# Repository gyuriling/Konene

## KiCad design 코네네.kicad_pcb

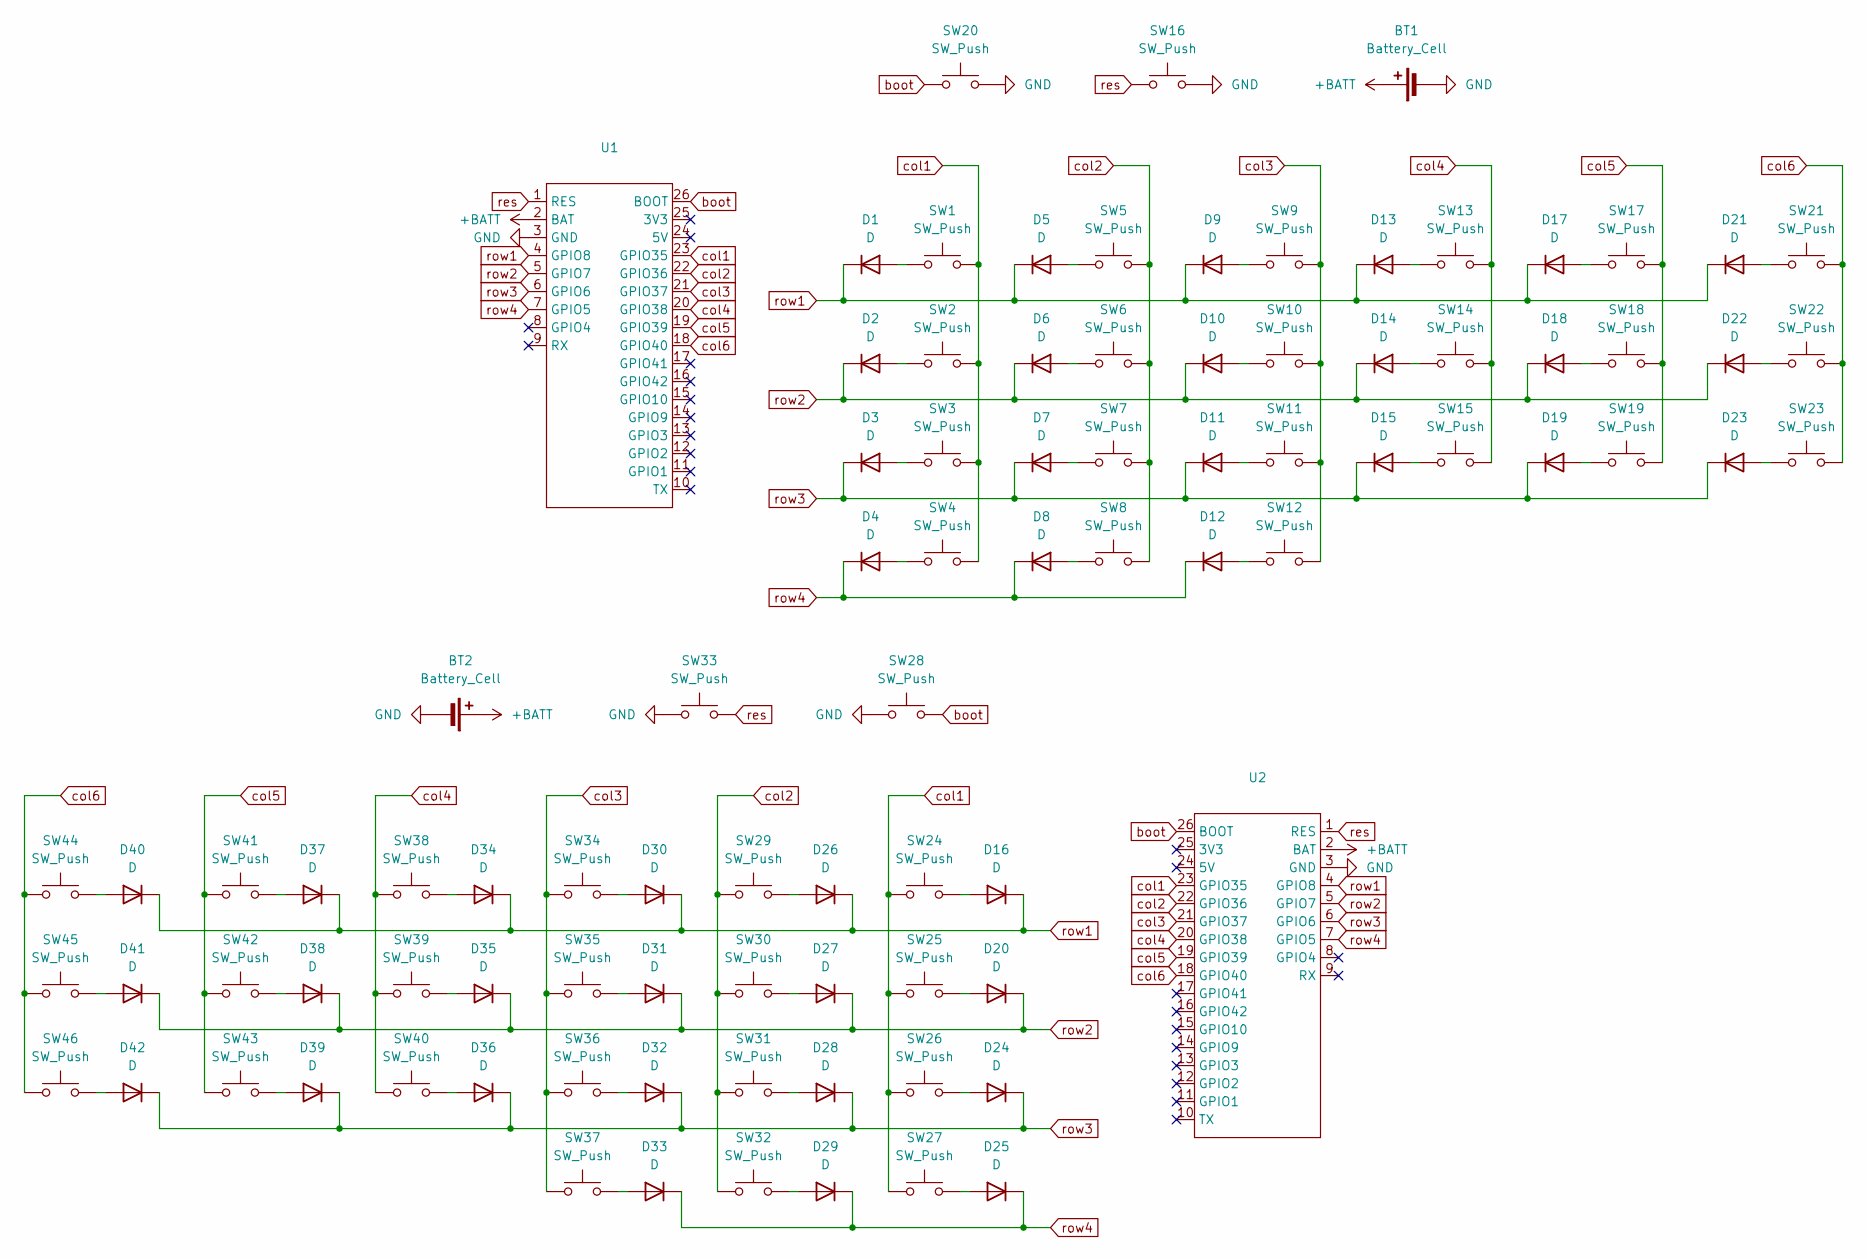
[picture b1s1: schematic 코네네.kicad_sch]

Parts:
BT1, BT2: Battery_Cell; AMASS_XT30U-M_1x02_P5.0mm_Vertical
D1, D2, D3, D4, D5, D6, D7, D8, D9, D10, D11, D12, D13, D14, D15, D16, D17, D18, D19, D20, D21, D22, D23, D24, D25, D26, D27, D28, D29, D30, D31, D32, D33, D34, D35, D36, D37, D38, D39, D40, D41, D42: D; D_SOD-123
SW1, SW2, SW3, SW4, SW5, SW6, SW7, SW8, SW9, SW10, SW11, SW12, SW13, SW14, SW15, SW17, SW18, SW19, SW21, SW22, SW23, SW24, SW25, SW26, SW27, SW29, SW30, SW31, SW32, SW34, SW35, SW36, SW37, SW38, SW39, SW40, SW41, SW42, SW43, SW44, SW45, SW46: SW_Push; Kailh_socket_PG1350
SW16, SW20, SW28, SW33: SW_Push; SW_PUSH_1P1T_6x3.5mm_H4.3_APEM_MJTP1243
U1, U2: esp32_displaykit_s3

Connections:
+BATT: BT1.1 (+), BT2.1 (+), U1.2 (BAT), U2.2 (BAT)
GND: BT1.2 (-), BT2.2 (-), SW16.2, SW20.2, SW28.2, SW33.2, U1.3 (GND), U2.3 (GND)
unnamed: D1.2 (A), SW1.1
unnamed: D2.2 (A), SW2.1
unnamed: D3.2 (A), SW3.1
unnamed: D4.2 (A), SW4.1
unnamed: D5.2 (A), SW5.1
unnamed: D6.2 (A), SW6.1
unnamed: D7.2 (A), SW7.1
unnamed: D8.2 (A), SW8.1
unnamed: D9.2 (A), SW9.1
unnamed: D10.2 (A), SW10.1
unnamed: D11.2 (A), SW11.1
unnamed: D12.2 (A), SW12.1
unnamed: D13.2 (A), SW13.1
unnamed: D14.2 (A), SW14.1
unnamed: D15.2 (A), SW15.1
unnamed: D16.2 (A), SW24.1
unnamed: D17.2 (A), SW17.1
unnamed: D18.2 (A), SW18.1
unnamed: D19.2 (A), SW19.1
unnamed: D20.2 (A), SW25.1
unnamed: D21.2 (A), SW21.1
unnamed: D22.2 (A), SW22.1
unnamed: D23.2 (A), SW23.1
unnamed: D24.2 (A), SW26.1
unnamed: D25.2 (A), SW27.1
unnamed: D26.2 (A), SW29.1
unnamed: D27.2 (A), SW30.1
unnamed: D28.2 (A), SW31.1
unnamed: D29.2 (A), SW32.1
unnamed: D30.2 (A), SW34.1
unnamed: D31.2 (A), SW35.1
unnamed: D32.2 (A), SW36.1
unnamed: D33.2 (A), SW37.1
unnamed: D34.2 (A), SW38.1
unnamed: D35.2 (A), SW39.1
unnamed: D36.2 (A), SW40.1
unnamed: D37.2 (A), SW41.1
unnamed: D38.2 (A), SW42.1
unnamed: D39.2 (A), SW43.1
unnamed: D40.2 (A), SW44.1
unnamed: D41.2 (A), SW45.1
unnamed: D42.2 (A), SW46.1
boot: SW20.1, SW28.1, U1.26 (BOOT), U2.26 (BOOT)
col1: SW1.2, SW2.2, SW3.2, SW4.2, SW24.2, SW25.2, SW26.2, SW27.2, U1.23 (GPIO35), U2.23 (GPIO35)
col2: SW5.2, SW6.2, SW7.2, SW8.2, SW29.2, SW30.2, SW31.2, SW32.2, U1.22 (GPIO36), U2.22 (GPIO36)
col3: SW9.2, SW10.2, SW11.2, SW12.2, SW34.2, SW35.2, SW36.2, SW37.2, U1.21 (GPIO37), U2.21 (GPIO37)
col4: SW13.2, SW14.2, SW15.2, SW38.2, SW39.2, SW40.2, U1.20 (GPIO38), U2.20 (GPIO38)
col5: SW17.2, SW18.2, SW19.2, SW41.2, SW42.2, SW43.2, U1.19 (GPIO39), U2.19 (GPIO39)
col6: SW21.2, SW22.2, SW23.2, SW44.2, SW45.2, SW46.2, U1.18 (GPIO40), U2.18 (GPIO40)
res: SW16.1, SW33.1, U1.1 (RES), U2.1 (RES)
row1: D1.1 (K), D5.1 (K), D9.1 (K), D13.1 (K), D16.1 (K), D17.1 (K), D21.1 (K), D26.1 (K), D30.1 (K), D34.1 (K), D37.1 (K), D40.1 (K), U1.4 (GPIO8), U2.4 (GPIO8)
row2: D2.1 (K), D6.1 (K), D10.1 (K), D14.1 (K), D18.1 (K), D20.1 (K), D22.1 (K), D27.1 (K), D31.1 (K), D35.1 (K), D38.1 (K), D41.1 (K), U1.5 (GPIO7), U2.5 (GPIO7)
row3: D3.1 (K), D7.1 (K), D11.1 (K), D15.1 (K), D19.1 (K), D23.1 (K), D24.1 (K), D28.1 (K), D32.1 (K), D36.1 (K), D39.1 (K), D42.1 (K), U1.6 (GPIO6), U2.6 (GPIO6)
row4: D4.1 (K), D8.1 (K), D12.1 (K), D25.1 (K), D29.1 (K), D33.1 (K), U1.7 (GPIO5), U2.7 (GPIO5)

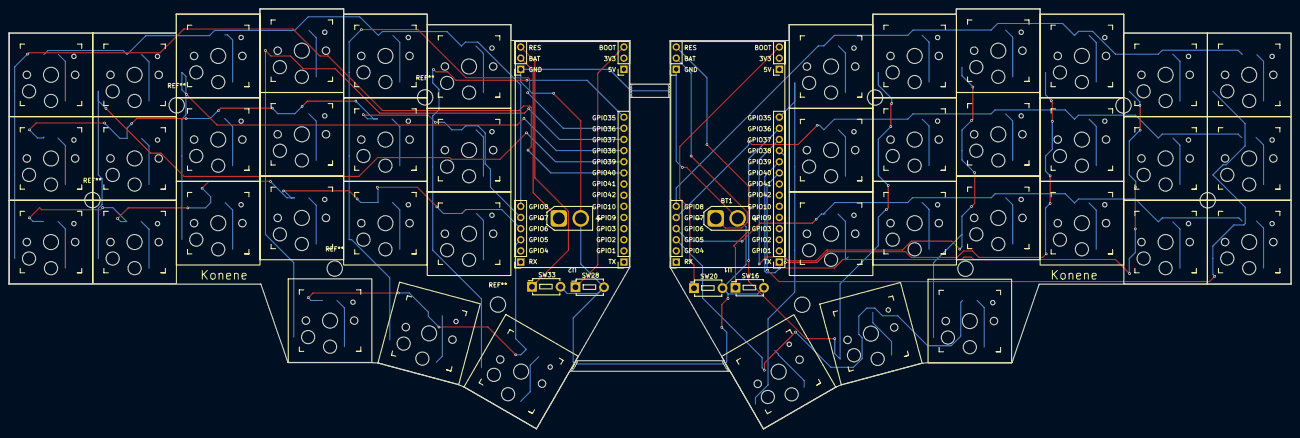
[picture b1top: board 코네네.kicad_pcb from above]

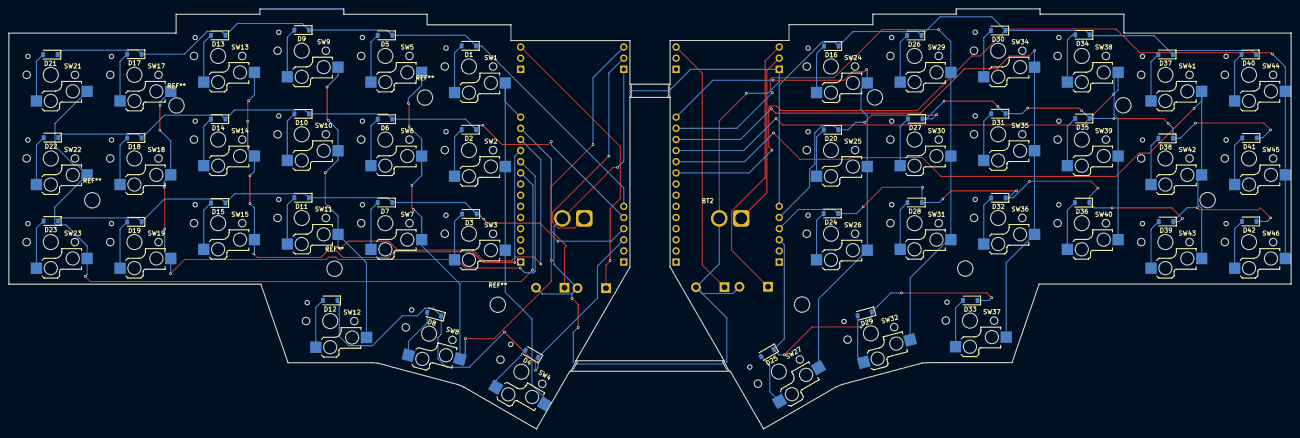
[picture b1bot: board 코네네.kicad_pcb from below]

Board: 2 copper layers, 292.1 x 95.7 mm, 92 parts (42 on the bottom side), 56 nets.

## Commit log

2025-08-07 왼쪽 판때기를 만들어따
2025-08-10 규멍을 뜌러따
